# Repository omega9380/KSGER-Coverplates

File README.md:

# KSGER Controller

T12 Soldering Iron control board.
A design based on schematics created by Mindstorm88 on the EEVBlog forums.

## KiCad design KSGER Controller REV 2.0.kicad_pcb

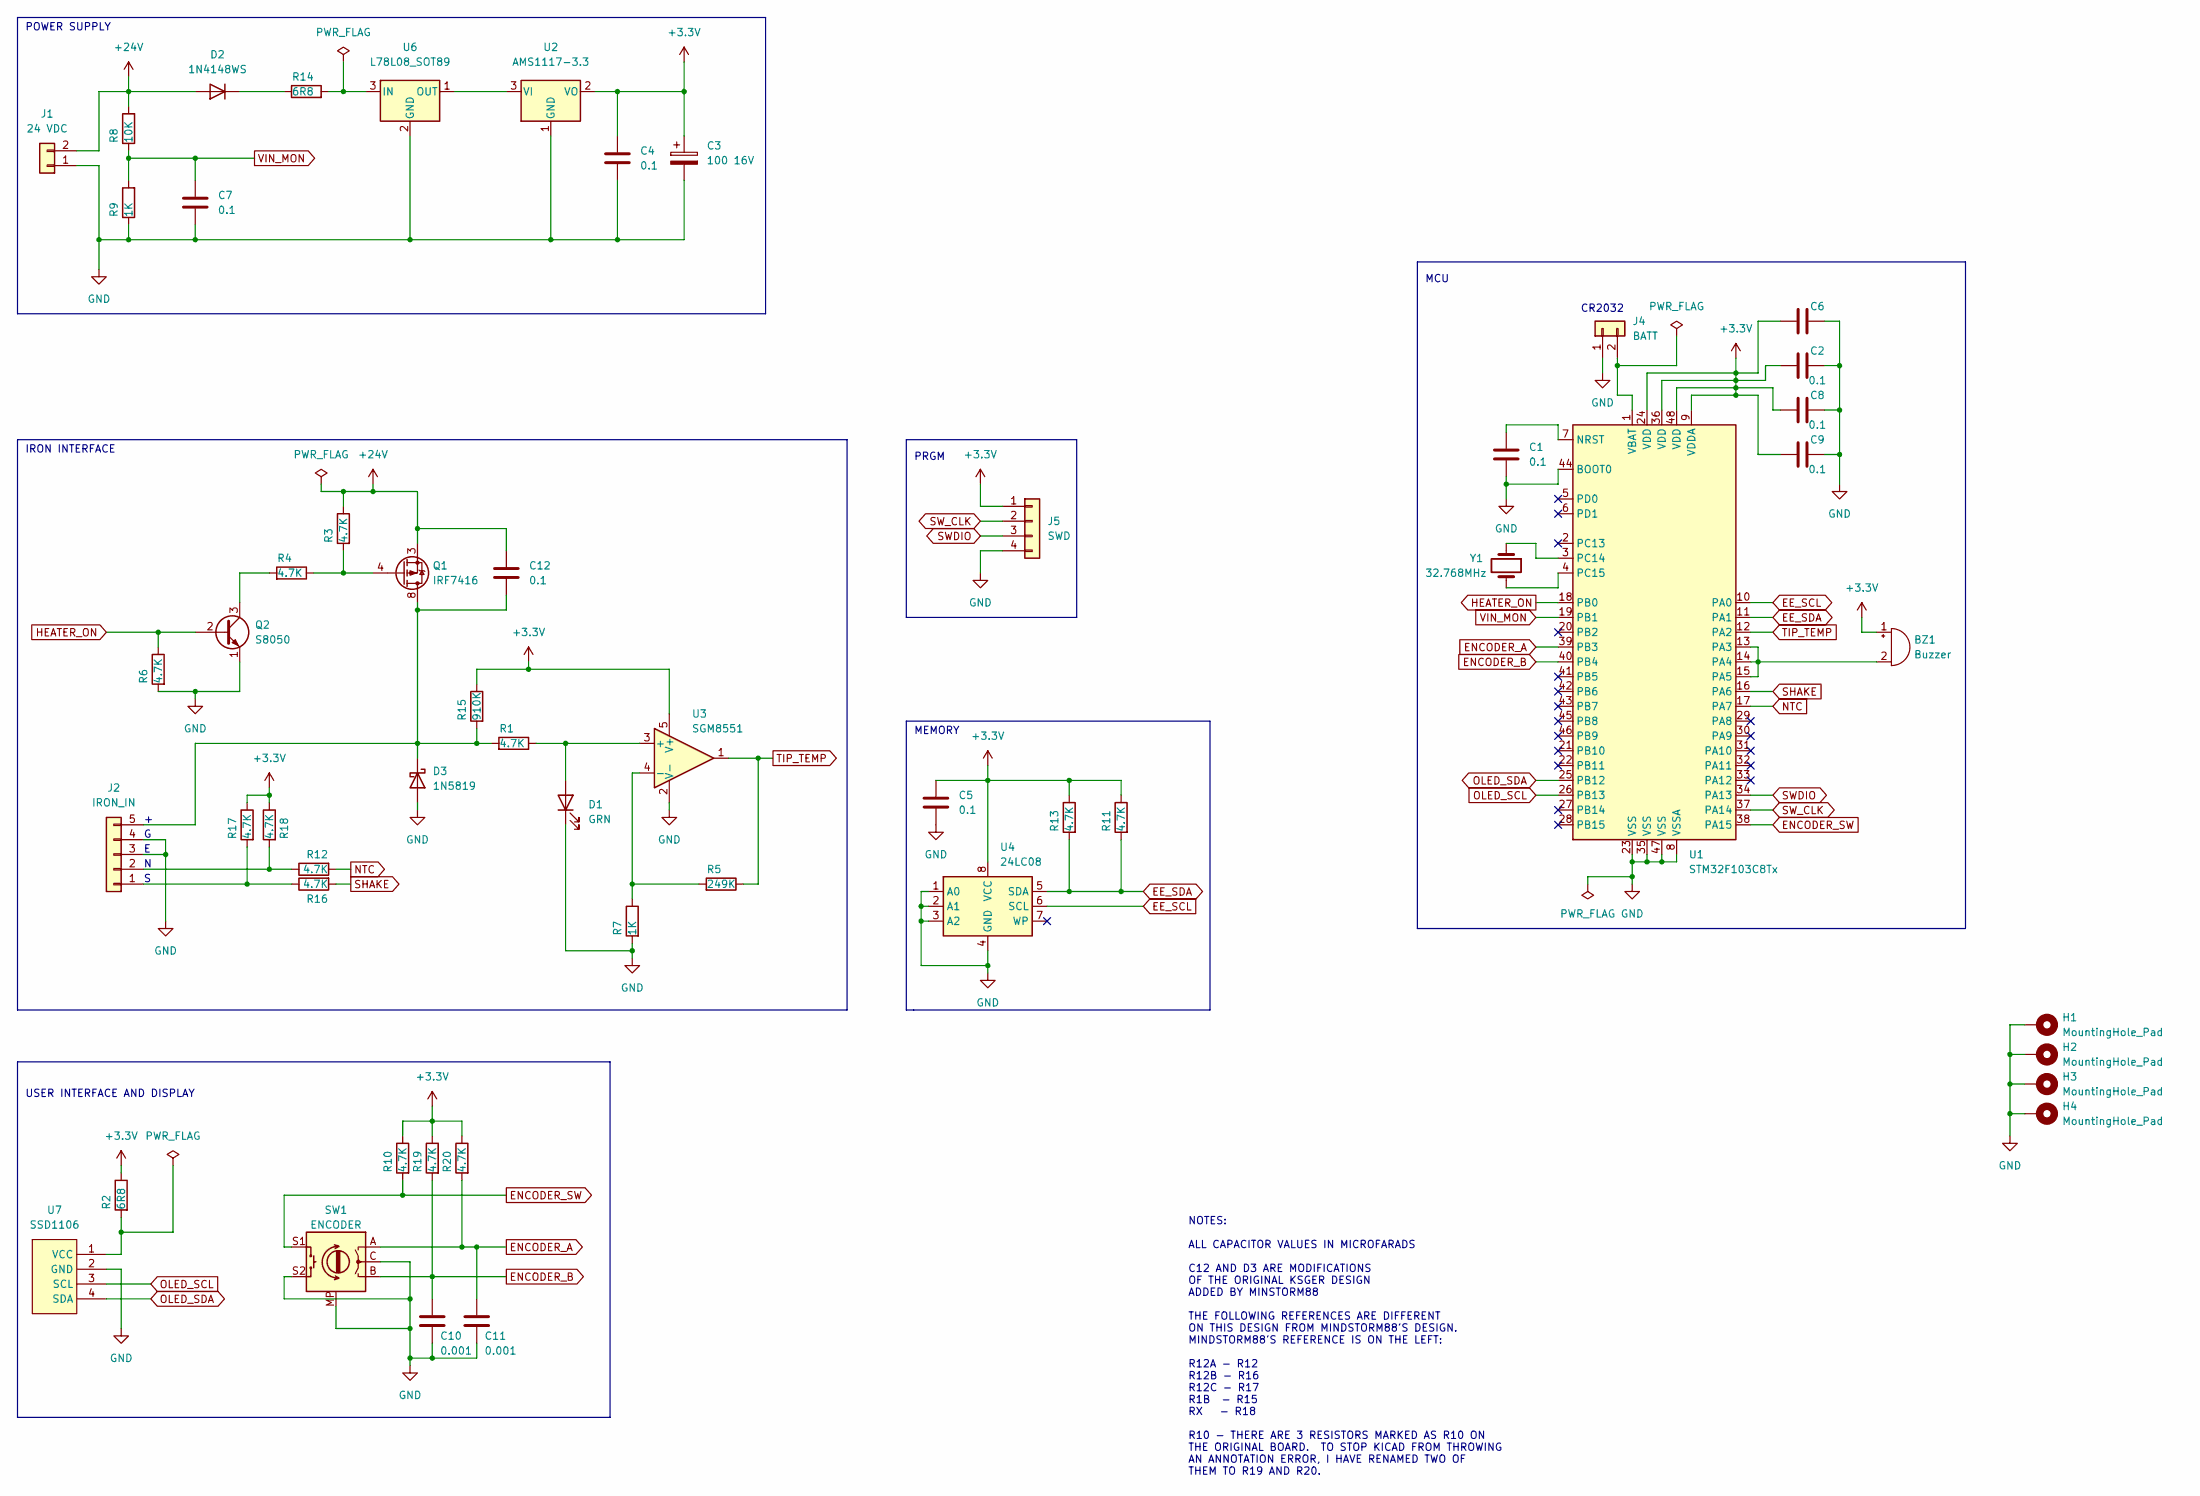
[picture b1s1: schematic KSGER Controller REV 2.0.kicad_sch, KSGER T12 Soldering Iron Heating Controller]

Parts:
BZ1: Buzzer; JST_EH_B2B-EH-A_1x02_P2.50mm_Vertical
C1, C4, C5, C7, C12: 0.1; C_0805_2012Metric
C2, C8, C9: 0.1; C_0201_0603Metric
C3: 100 16V; CP_EIA-7343-31_Kemet-D
C6: (no value)
C10, C11: 0.001; C_0805_2012Metric
D1: GRN; LED_0603_1608Metric
D2: 1N4148WS; D_SOD-323
D3: 1N5819; D_SOD-323
H1, H2, H3, H4: MountingHole_Pad; MountingHole_3.2mm_M3_Pad_Via
J1: 24 VDC; JST_EH_B2B-EH-A_1x02_P2.50mm_Vertical
J2: IRON_IN; JST_EH_B5B-EH-A_1x05_P2.50mm_Vertical
J4: BATT; JST_EH_B2B-EH-A_1x02_P2.50mm_Vertical
J5: SWD; JST_EH_B4B-EH-A_1x04_P2.50mm_Vertical
Q1: IRF7416; SO-8_3.9x4.9mm_P1.27mm
Q2: S8050; SOT-23
R1, R3, R4, R6, R10, R11, R12, R13, R16, R17, R18, R19, R20: 4.7K; R_0603_1608Metric
R2, R14: 6R8; R_0603_1608Metric
R5: 249K; R_0805_2012Metric
R7, R9: 1K; R_0603_1608Metric
R8: 10K; R_0603_1608Metric
R15: 910K; R_0805_2012Metric
SW1: ENCODER; RotaryEncoder_Alps_EC11E-Switch_Vertical_H20mm
U1: STM32F103C8Tx; LQFP-48_7x7mm_P0.5mm
U2: AMS1117-3.3; SOT-223-3_TabPin2
U3: SGM8551; SOT-23-5
U4: 24LC08; SOP-8_3.9x4.9mm_P1.27mm
U6: L78L08_SOT89; SOT-89-3
U7: SSD1106
Y1: 32.768MHz; Crystal_SMD_3215-2Pin_3.2x1.5mm

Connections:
+24V: C12.1, D2.2 (A), J1.2, Q1.1, Q1.2, Q1.3, R3.1, R8.2
EE_SCL: U1.10 (PA0), U4.6 (SCL)
EE_SDA: R11.2, R13.2, U1.11 (PA1), U4.5 (SDA)
ENCODER_A: C11.1, R20.2, SW1.A, U1.39 (PB3)
ENCODER_B: C10.1, R19.2, SW1.B, U1.40 (PB4)
ENCODER_SW: R10.2, SW1.S1, U1.38 (PA15)
GND: C1.2, C2.2, C3.2, C4.2, C5.2, C6.2, C7.2, C8.2, C9.2, C10.2, C11.2, D1.1 (K), D3.2 (A), H1.1, H2.1, H3.1, H4.1, J1.1, J2.3, J2.4, J4.1, J5.4, Q2.1 (E), R6.2, R7.2, R9.1, SW1.C, SW1.MP, SW1.S2, U1.8 (VSSA), U1.23 (VSS), U1.35 (VSS), U1.44 (BOOT0), U1.47 (VSS), U2.1 (GND), U3.2 (V-), U4.1 (A0), U4.2 (A1), U4.3 (A2), U4.4 (GND), U6.2 (GND), U7.2 (GND)
HEATER_ON: Q2.2 (B), R6.1, U1.18 (PB0)
NTC: R12.2, U1.17 (PA7)
unnamed: BZ1.2 (+), U1.13 (PA3), U1.14 (PA4), U1.15 (PA5)
unnamed: C1.1, U1.7 (NRST)
unnamed: C12.2, D3.1 (K), J2.5, Q1.5, Q1.6, Q1.7, Q1.8, R1.2, R15.2
unnamed: D1.2 (A), R1.1, U3.3 (+)
unnamed: D2.1 (K), R14.1
unnamed: J2.1, R16.1, R17.2
unnamed: J2.2, R12.1, R18.2
unnamed: J4.2, U1.1 (VBAT)
unnamed: Q1.4, R3.2, R4.1
unnamed: Q2.3 (C), R4.2
unnamed: R2.2, U7.1 (VCC)
unnamed: R5.2, R7.1, U3.4 (-)
unnamed: R14.2, U6.3 (IN)
unnamed: U1.3 (PC14), Y1.1
unnamed: U1.4 (PC15), Y1.2
unnamed: U2.3 (VI), U6.1 (OUT)
OLED_SCL: U1.26 (PB13), U7.3 (SCL)
OLED_SDA: U1.25 (PB12), U7.4 (SDA)
SHAKE: R16.2, U1.16 (PA6)
SWDIO: J5.3, U1.34 (PA13)
SW_CLK: J5.2, U1.37 (PA14)
TIP_TEMP: R5.1, U1.12 (PA2), U3.1
VIN_MON: C7.1, R8.1, R9.2, U1.19 (PB1)

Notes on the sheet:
USER INTERFACE AND DISPLAY
PRGM
POWER SUPPLY
MCU
IRON INTERFACE
CR2032
MEMORY
NOTES: ALL CAPACITOR VALUES IN MICROFARADS C12 AND D3 ARE MODIFICATIONS OF THE ORIGINAL KSGER DESIGN ADDED BY MINSTORM88 THE FOLLOWING REFERENCES ARE DIFFERENT ON THIS DESIGN FROM MINDSTORM88'S DESIGN. MINDSTORM88'S REFERENCE IS ON THE LEFT: R12A - R12 R12B - R16 R12C - R17 R1B - R15 RX - R18 R10 -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

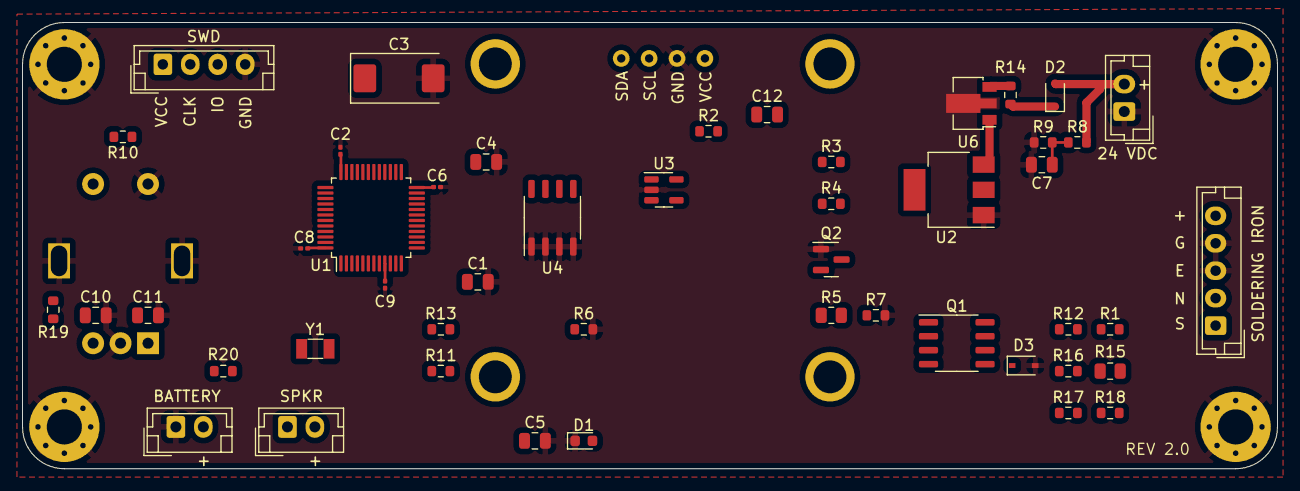
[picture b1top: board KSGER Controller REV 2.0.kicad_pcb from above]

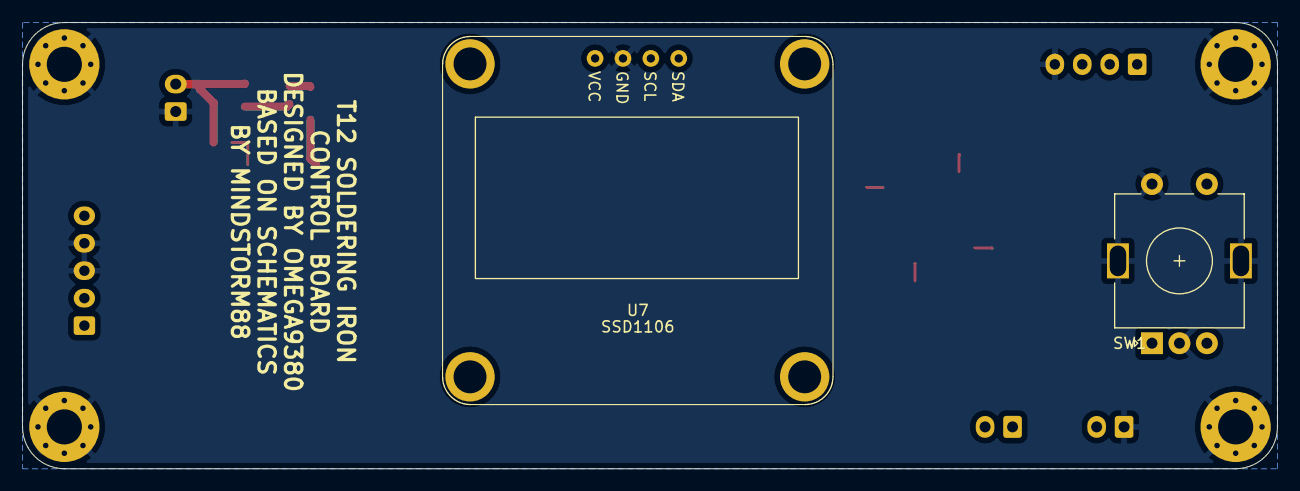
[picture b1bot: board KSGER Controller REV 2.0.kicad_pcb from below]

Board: 2 copper layers, 114.3 x 40.6 mm, 54 parts (2 on the bottom side), 33 nets.

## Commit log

2022-04-28 Working on controller schematic
2022-04-28 Done for the day
2022-04-28 Done for the night
2022-05-04 Other
2022-05-04 Finished schematic
2022-05-04 more playing around
2022-05-04 Started working on PCB
2022-05-04 Moar board work
2022-05-05 Added C5 and C6 from flobbydusts schematic
2022-05-05 Added PWR_FLAGs to resolve some ERC errors
2022-05-05 Minor visual changes
2022-05-05 Updated C10 and C11 to 1nF
2022-05-05 Added cap value note
2022-05-05 Finished traces on board
2022-05-05 Final touches to board layout
2022-05-05 Fixed up folder heierarchy, brought controller board to front
2022-05-05 Generated BOM
2022-05-05 Updated PDF
2022-05-05 Generate JLCPCB gerbers
2022-05-05 Playing with trace widths
2022-05-06 Adjusting traces again
2022-05-06 Created rev 2.0 to redo the board layout based on feedback on the EEVBlog forums
2022-05-06 Removed all traces to start from scratch!
2022-05-06 Working on trace redesign for v2
2022-05-06 Autosave
2022-05-07 Rev 2 PDF
2022-05-07 REV2
